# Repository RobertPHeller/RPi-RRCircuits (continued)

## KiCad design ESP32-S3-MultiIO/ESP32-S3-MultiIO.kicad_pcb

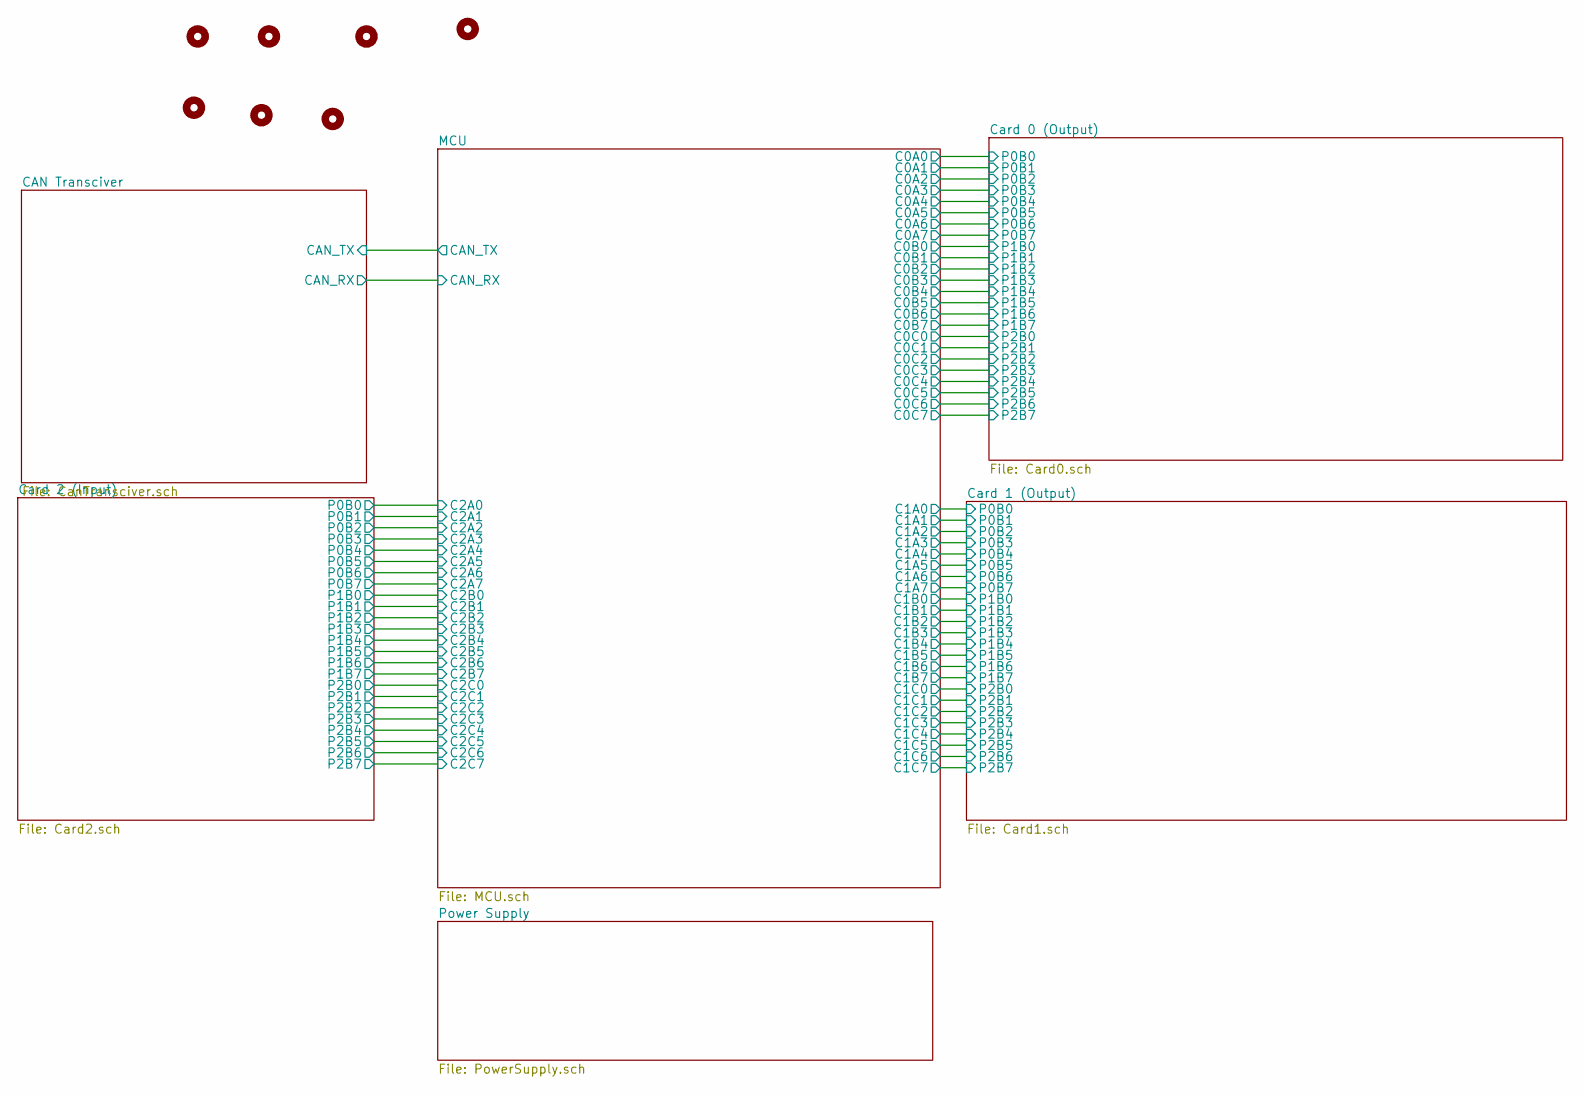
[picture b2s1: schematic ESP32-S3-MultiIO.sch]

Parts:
FD101, FD102, FD103: Fid Mark; Fiducial_Modern_SilkscreenTop
MK101, MK102, MK103, MK104: Mounting_Hole; MountingHole_3.5mm

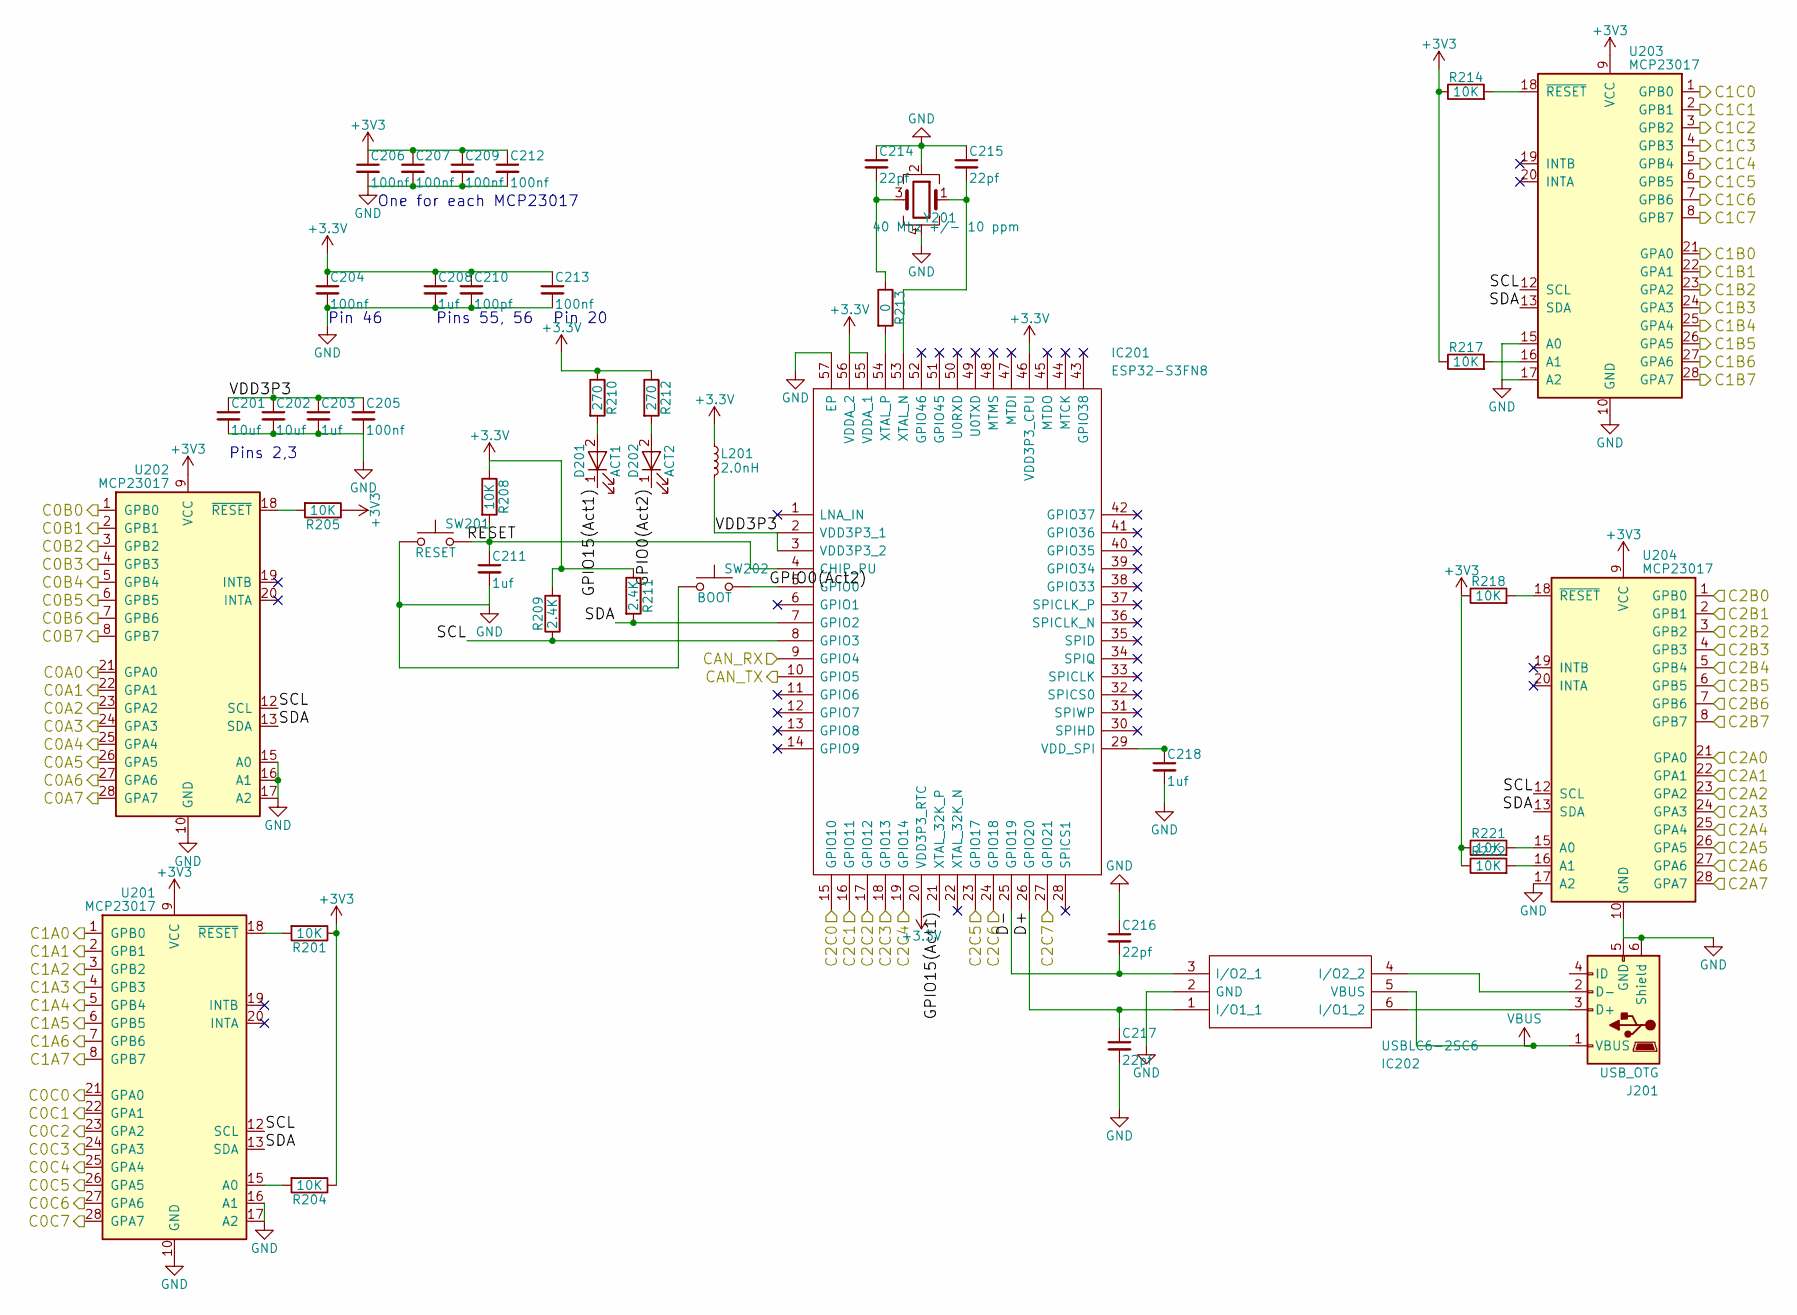
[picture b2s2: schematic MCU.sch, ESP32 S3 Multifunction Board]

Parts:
C201, C202: 10uf; C_0805; Mouser Part Number 187-CL21A106MQFNNNE
C203, C208, C211, C218: 1uf; C_0402; Mouser Part Number 80-C0402C101K8RAUTO
C204, C205, C206, C207, C209, C212, C213: 100nf; C_0402; Mouser Part Number 710-885012105001
C210: 100pf; C_0402; Mouser Part Number 80-C0402C101K3RAUTO
C214, C215, C216, C217: 22pf; C_0402; Mouser Part Number 187-CL05C220JB5NNND
D201: ACT1; LED_0402; Mouser Part Number 710-150040GS73220
D202: ACT2; LED_0402; Mouser Part Number 710-150040SS73220
IC201: ESP32-S3FN8; QFN-56-1EP_7x7mm_Pitch0.4mm; Manufacturer_Part_Number ESP32-S3FN8; Mouser Part Number 356-ESP32-S3FN8
IC202: USBLC6-2SC6; SOT-23-6; Mouser Part Number 511-USBLC6-2SC6
J201: USB_OTG; USB_Micro-B_Molex_47346-0001; Mouser Part Number 538-47346-0001
L201: 2.0nH; L_0402; Mouser Part Number 810-MLG1005S2N0ST000
R201, R204, R205, R208, R214, R217, R218, R221, R222: 10K; R_0402; Mouser Part Number 603-RC0402JR-1310KL
R209, R211: 2.4K; R_0402; Mouser Part Number 71-CRCW06032K40JNEAC
R210, R212: 270; R_0402; Mouser Part Number 754-RR0510P-271D
R213: 0; R_0402; Mouser Part Number 71-CRCW04020000Z0EDC
SW201: RESET; PTS647SM38SMTR2LFS; Mouser Part Number 611-PTS647SN70SMTR2L
SW202: BOOT; PTS647SM38SMTR2LFS; Mouser Part Number 611-PTS647SN70SMTR2L
U201, U202, U203, U204: MCP23017; SOIC-28W_7.5x17.9mm_Pitch1.27mm
Y201: 40 Mhz +/- 10 ppm; FA20_H; Mouser Part Number 732-FA-20H40MF10Z-W3

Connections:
/CAN Transciver/CAN_RX: IC201.9 (GPIO4); also elsewhere on the board
/CAN Transciver/CAN_TX: IC201.10 (GPIO5); also elsewhere on the board
/MCU/C0A0: U202.21 (GPA0); also elsewhere on the board
/MCU/C0A1: U202.22 (GPA1); also elsewhere on the board
/MCU/C0A2: U202.23 (GPA2); also elsewhere on the board
/MCU/C0A3: U202.24 (GPA3); also elsewhere on the board
/MCU/C0A4: U202.25 (GPA4); also elsewhere on the board
/MCU/C0A5: U202.26 (GPA5); also elsewhere on the board
/MCU/C0A6: U202.27 (GPA6); also elsewhere on the board
/MCU/C0A7: U202.28 (GPA7); also elsewhere on the board
/MCU/C0B0: U202.1 (GPB0); also elsewhere on the board
/MCU/C0B1: U202.2 (GPB1); also elsewhere on the board
/MCU/C0B2: U202.3 (GPB2); also elsewhere on the board
/MCU/C0B3: U202.4 (GPB3); also elsewhere on the board
/MCU/C0B4: U202.5 (GPB4); also elsewhere on the board
/MCU/C0B5: U202.6 (GPB5); also elsewhere on the board
/MCU/C0B6: U202.7 (GPB6); also elsewhere on the board
/MCU/C0B7: U202.8 (GPB7); also elsewhere on the board
/MCU/C0C0: U201.21 (GPA0); also elsewhere on the board
/MCU/C0C1: U201.22 (GPA1); also elsewhere on the board
/MCU/C0C2: U201.23 (GPA2); also elsewhere on the board
/MCU/C0C3: U201.24 (GPA3); also elsewhere on the board
/MCU/C0C4: U201.25 (GPA4); also elsewhere on the board
/MCU/C0C5: U201.26 (GPA5); also elsewhere on the board
/MCU/C0C6: U201.27 (GPA6); also elsewhere on the board
/MCU/C0C7: U201.28 (GPA7); also elsewhere on the board
/MCU/C1A0: U201.1 (GPB0); also elsewhere on the board
/MCU/C1A1: U201.2 (GPB1); also elsewhere on the board
/MCU/C1A2: U201.3 (GPB2); also elsewhere on the board
/MCU/C1A3: U201.4 (GPB3); also elsewhere on the board
/MCU/C1A4: U201.5 (GPB4); also elsewhere on the board
/MCU/C1A5: U201.6 (GPB5); also elsewhere on the board
/MCU/C1A6: U201.7 (GPB6); also elsewhere on the board
/MCU/C1A7: U201.8 (GPB7); also elsewhere on the board
/MCU/C1B0: U203.21 (GPA0); also elsewhere on the board
/MCU/C1B1: U203.22 (GPA1); also elsewhere on the board
/MCU/C1B2: U203.23 (GPA2); also elsewhere on the board
/MCU/C1B3: U203.24 (GPA3); also elsewhere on the board
/MCU/C1B4: U203.25 (GPA4); also elsewhere on the board
/MCU/C1B5: U203.26 (GPA5); also elsewhere on the board
/MCU/C1B6: U203.27 (GPA6); also elsewhere on the board
/MCU/C1B7: U203.28 (GPA7); also elsewhere on the board
/MCU/C1C0: U203.1 (GPB0); also elsewhere on the board
/MCU/C1C1: U203.2 (GPB1); also elsewhere on the board
/MCU/C1C2: U203.3 (GPB2); also elsewhere on the board
/MCU/C1C3: U203.4 (GPB3); also elsewhere on the board
/MCU/C1C4: U203.5 (GPB4); also elsewhere on the board
/MCU/C1C5: U203.6 (GPB5); also elsewhere on the board
/MCU/C1C6: U203.7 (GPB6); also elsewhere on the board
/MCU/C1C7: U203.8 (GPB7); also elsewhere on the board
/MCU/C2A0: U204.21 (GPA0); also elsewhere on the board
/MCU/C2A1: U204.22 (GPA1); also elsewhere on the board
/MCU/C2A2: U204.23 (GPA2); also elsewhere on the board
/MCU/C2A3: U204.24 (GPA3); also elsewhere on the board
/MCU/C2A4: U204.25 (GPA4); also elsewhere on the board
/MCU/C2A5: U204.26 (GPA5); also elsewhere on the board
/MCU/C2A6: U204.27 (GPA6); also elsewhere on the board
/MCU/C2A7: U204.28 (GPA7); also elsewhere on the board
/MCU/C2B0: U204.1 (GPB0); also elsewhere on the board
/MCU/C2B1: U204.2 (GPB1); also elsewhere on the board
/MCU/C2B2: U204.3 (GPB2); also elsewhere on the board
/MCU/C2B3: U204.4 (GPB3); also elsewhere on the board
/MCU/C2B4: U204.5 (GPB4); also elsewhere on the board
/MCU/C2B5: U204.6 (GPB5); also elsewhere on the board
/MCU/C2B6: U204.7 (GPB6); also elsewhere on the board
/MCU/C2B7: U204.8 (GPB7); also elsewhere on the board
/MCU/C2C0: IC201.15 (GPIO10); also elsewhere on the board
/MCU/C2C1: IC201.16 (GPIO11); also elsewhere on the board
/MCU/C2C2: IC201.17 (GPIO12); also elsewhere on the board
/MCU/C2C3: IC201.18 (GPIO13); also elsewhere on the board
/MCU/C2C4: IC201.19 (GPIO14); also elsewhere on the board
/MCU/C2C5: IC201.23 (GPIO17); also elsewhere on the board
/MCU/C2C6: IC201.24 (GPIO18); also elsewhere on the board
/MCU/C2C7: IC201.27 (GPIO21); also elsewhere on the board
/MCU/D+: C217.1, IC201.26 (GPIO20), IC202.1 (I/O1_1)
/MCU/D-: C216.2, IC201.25 (GPIO19), IC202.3 (I/O2_1)
/MCU/GPIO0(Act2): D202.1 (K), IC201.5 (GPIO0), SW202.2
/MCU/GPIO15(Act1): D201.1 (K), IC201.21 (XTAL_32K_P)
/MCU/RESET: C211.1, IC201.4 (CHIP_PU), R208.2, SW201.2
/MCU/SCL: IC201.8 (GPIO3), R209.1, U201.12 (SCL), U202.12 (SCL), U203.12 (SCL), U204.12 (SCL)
/MCU/SDA: IC201.7 (GPIO2), R211.2, U201.13 (SDA), U202.13 (SDA), U203.13 (SDA), U204.13 (SDA)
/MCU/VDD3P3: C201.1, C202.1, C203.1, C205.1, IC201.2 (VDD3P3_1), IC201.3 (VDD3P3_2), L201.2
GND: C201.2, C202.2, C203.2, C204.2, C205.2, C206.2, C207.2, C208.2, C209.2, C210.2, C211.2, C212.2, C213.2, C214.1, C215.1, C216.1, C217.2, C218.2, IC201.57 (EP), IC202.2 (GND), J201.5 (GND), J201.6 (Shield), SW201.1, SW202.1, U201.10 (GND), U201.16 (A1), U201.17 (A2), U202.10 (GND), U202.15 (A0), U202.16 (A1), U202.17 (A2), U203.10 (GND), U203.15 (A0), U203.17 (A2), U204.10 (GND), U204.17 (A2), Y201.2, Y201.4; also elsewhere on the board
unnamed: C214.2, R213.1, Y201.3
unnamed: C215.2, IC201.53 (XTAL_N), Y201.1
unnamed: C218.1, IC201.29 (VDD_SPI)
unnamed: D201.2 (A), R210.2
unnamed: D202.2 (A), R212.2
unnamed: IC201.54 (XTAL_P), R213.2
unnamed: IC202.4 (I/O2_2), J201.2 (D-)
unnamed: IC202.6 (I/O1_2), J201.3 (D+)
unnamed: R201.2, U201.18 (~RESET)
unnamed: R204.2, U201.15 (A0)
unnamed: R205.2, U202.18 (~RESET)
unnamed: R214.2, U203.18 (~RESET)
unnamed: R217.2, U203.16 (A1)
unnamed: R218.2, U204.18 (~RESET)
unnamed: R221.2, U204.15 (A0)
unnamed: R222.2, U204.16 (A1)
VBUS: IC202.5 (VBUS), J201.1 (VBUS)

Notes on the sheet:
Pins 2,3
Pin 46
Pins 55, 56
Pin 20
One for each MCP23017

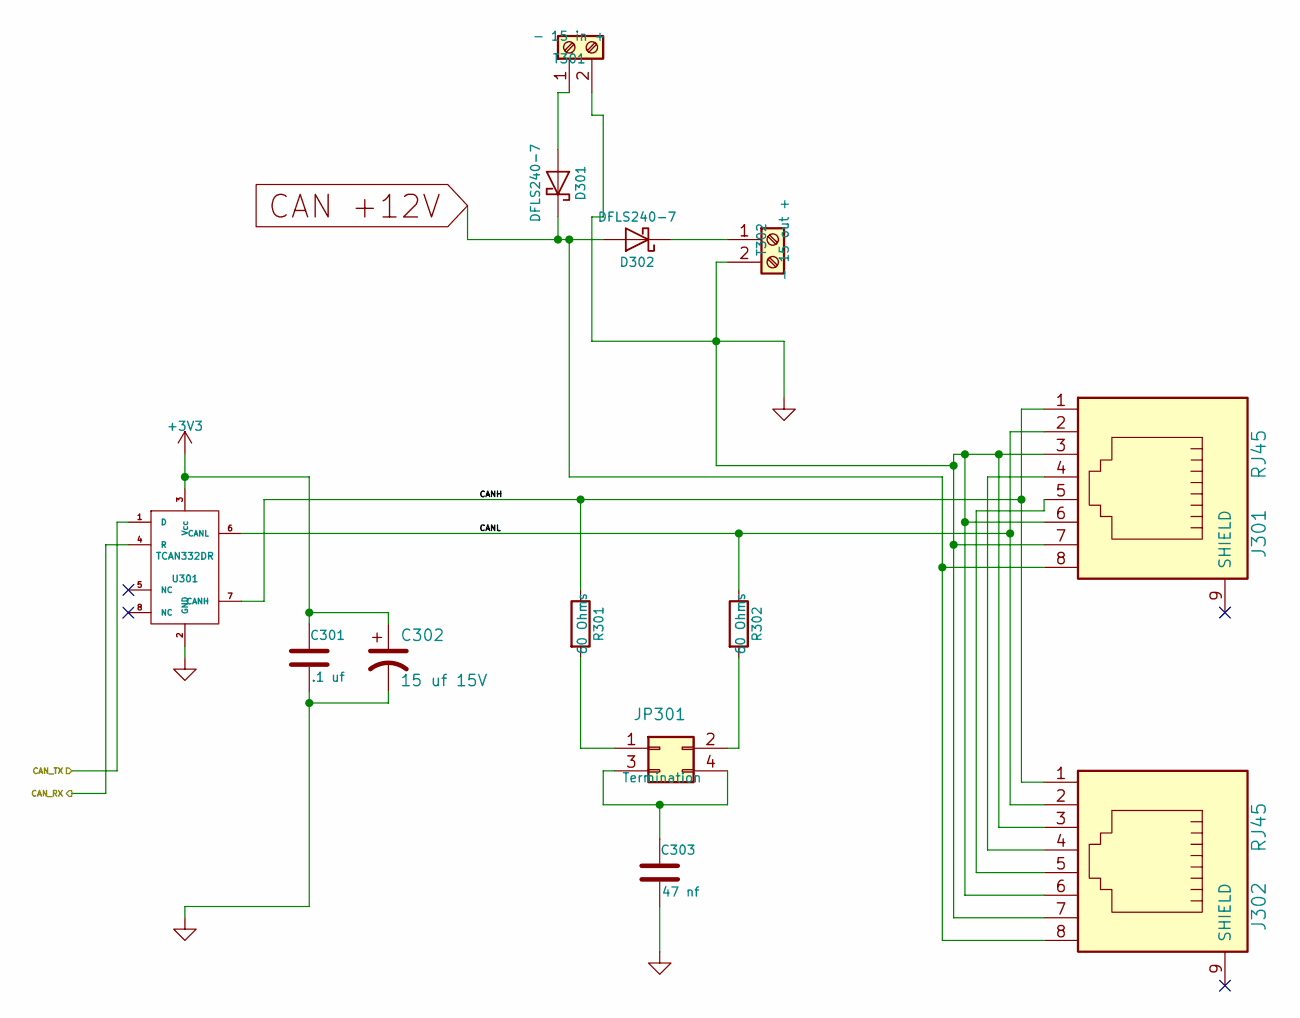
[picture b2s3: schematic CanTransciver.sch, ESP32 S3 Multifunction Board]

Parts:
C301: .1 uf; C_0603; Mouser Part Number 710-885012206095
C302: 15 uf 15V; CP_Elec_4x5.7; Mouser Part Number 647-UUD1C150MCL
C303: 47 nf; C_0603; Mouser Part Number 710-885012206093
D301, D302: DFLS240-7; D_PowerDI-123; Mouser Part Number 621-DFLS240-7
J301, J302: RJ45; RJ45_8N-S; Mouser Part Number 710-615008144221
JP301: Termination; Pin_Header_Straight_2x02_Pitch2.54mm; Mouser Part Number 649-67997-404HLF
R301, R302: 60 Ohms; R_1206; Mouser Part Number 71-CRCW120660R0KNAIF
T301: - 15 in +; TerminalBlock_Pheonix_MPT-2.54mm_2pol; Mouser Part Number 651-1725656
T302: - 15 out +; TerminalBlock_Pheonix_MPT-2.54mm_2pol; Mouser Part Number 651-1725656
U301: TCAN332DR; SOIC-8_3.9x4.9mm_Pitch1.27mm; Mouser Part Number 595-TCAN332DR

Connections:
/CAN Transciver/CANH: J301.1, J302.1, R301.1, U301.7 (CANH)
/CAN Transciver/CANL: J301.2, J302.2, R302.1, U301.6 (CANL)
/CAN Transciver/CAN_RX: U301.4 (R); also elsewhere on the board
/CAN Transciver/CAN_TX: U301.1 (D); also elsewhere on the board
CAN +12V: D301.1 (K), D302.2 (A), J301.8, J302.8; also elsewhere on the board
GND: C301.2, C302.2, C303.2, J301.3, J301.6, J301.7, J302.3, J302.6, J302.7, T301.2, T302.2, U301.2 (GND); also elsewhere on the board
unnamed: C303.1, JP301.3, JP301.4
unnamed: D301.2 (A), T301.1
unnamed: D302.1 (K), T302.1
unnamed: J301.4, J302.4
unnamed: J301.5, J302.5
unnamed: JP301.1, R301.2
unnamed: JP301.2, R302.2

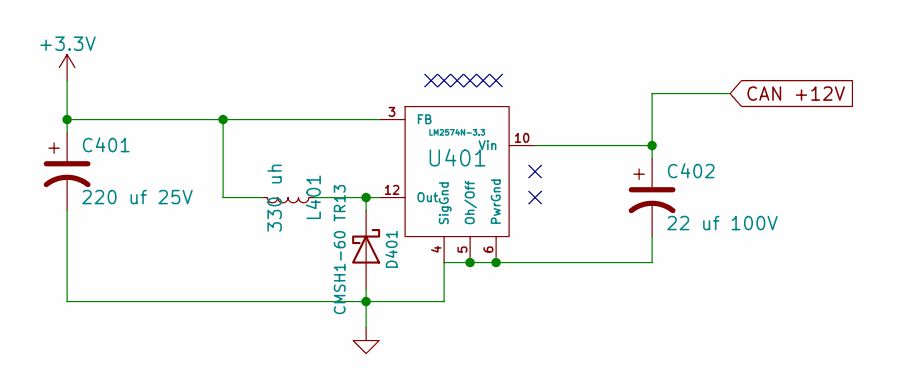
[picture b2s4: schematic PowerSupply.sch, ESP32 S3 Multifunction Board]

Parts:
C401: 220 uf 25V; CP_Elec_8x10; Mouser Part Number 647-UWT1E221MNL1GS
C402: 22 uf 100V; CP_Elec_8x10; Mouser Part Number 647-UUX2A220MNL6GS
D401: CMSH1-60 TR13; D_SMB; Mouser Part Number 610-CMSH1-60TR13
L401: 330 uh; SRN1060; Mouser Part Number 652-SRN1060-331M
U401: LM2574N-3.3; SOIC-14_7.4x8.7mm_Pitch1.27mm; Mouser Part Number 926-LM2574MX33NOPB

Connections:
CAN +12V: C402.1, U401.10 (Vin); also elsewhere on the board
GND: C401.2, C402.2, D401.2 (A), U401.4 (SigGnd), U401.5 (Oh/Off), U401.6 (PwrGnd); also elsewhere on the board
unnamed: D401.1 (K), L401.1, U401.12 (Out)

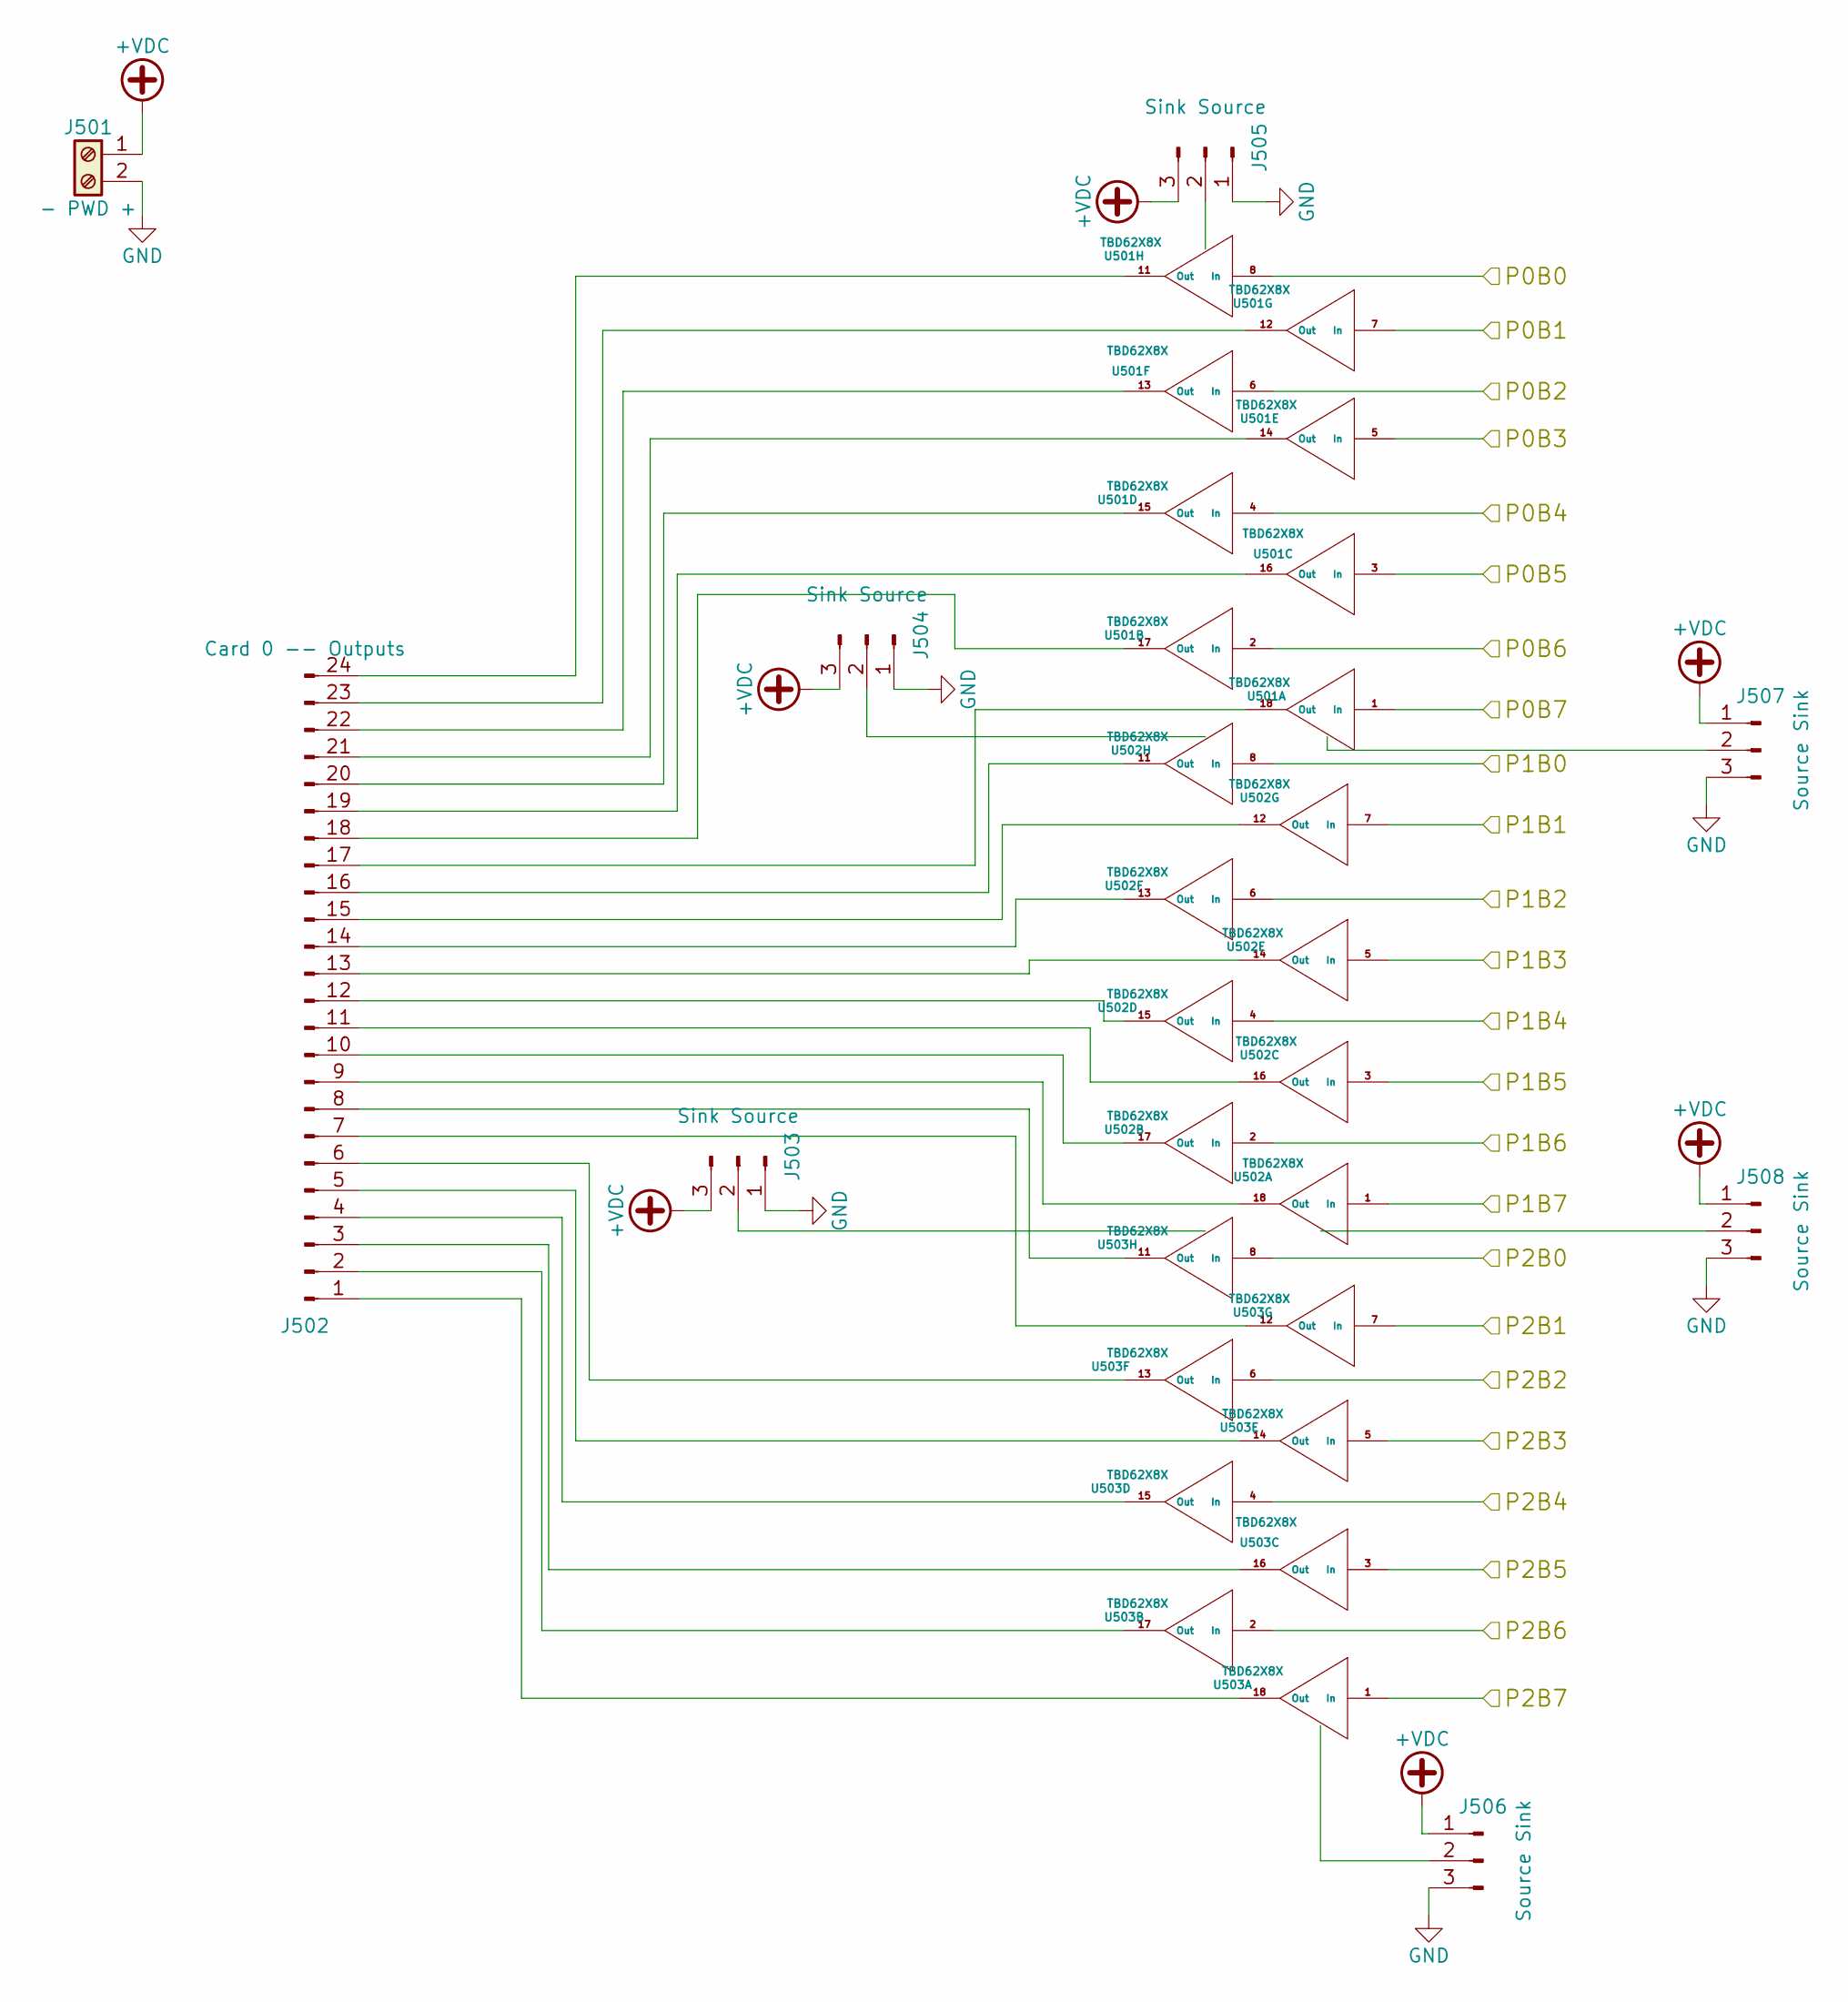
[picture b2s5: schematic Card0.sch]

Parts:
J501: - PWD +; TerminalBlock_Pheonix_MPT-2.54mm_2pol
J502: Card 0 -- Outputs; Molex_KK_396_01x24_3.96mm_RightAngle; Mouser Part Number 538-26-48-1242
J503, J504, J505: Sink Source; Pin_Header_Straight_1x03_Pitch2.54mm
J506, J507, J508: Source Sink; Pin_Header_Straight_1x03_Pitch2.54mm
U501, U502, U503: TBD62X8X; DIP-18_W7.62mm; Mouser Part Number 571-1-2199298-5

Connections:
+VDC: J501.1, J503.3, J504.3, J505.3, J506.1, J507.1, J508.1; also elsewhere on the board
/MCU/C0A0: U501.8 (In); also elsewhere on the board
/MCU/C0A1: U501.7 (In); also elsewhere on the board
/MCU/C0A2: U501.6 (In); also elsewhere on the board
/MCU/C0A3: U501.5 (In); also elsewhere on the board
/MCU/C0A4: U501.4 (In); also elsewhere on the board
/MCU/C0A5: U501.3 (In); also elsewhere on the board
/MCU/C0A6: U501.2 (In); also elsewhere on the board
/MCU/C0A7: U501.1 (In); also elsewhere on the board
/MCU/C0B0: U502.8 (In); also elsewhere on the board
/MCU/C0B1: U502.7 (In); also elsewhere on the board
/MCU/C0B2: U502.6 (In); also elsewhere on the board
/MCU/C0B3: U502.5 (In); also elsewhere on the board
/MCU/C0B4: U502.4 (In); also elsewhere on the board
/MCU/C0B5: U502.3 (In); also elsewhere on the board
/MCU/C0B6: U502.2 (In); also elsewhere on the board
/MCU/C0B7: U502.1 (In); also elsewhere on the board
/MCU/C0C0: U503.8 (In); also elsewhere on the board
/MCU/C0C1: U503.7 (In); also elsewhere on the board
/MCU/C0C2: U503.6 (In); also elsewhere on the board
/MCU/C0C3: U503.5 (In); also elsewhere on the board
/MCU/C0C4: U503.4 (In); also elsewhere on the board
/MCU/C0C5: U503.3 (In); also elsewhere on the board
/MCU/C0C6: U503.2 (In); also elsewhere on the board
/MCU/C0C7: U503.1 (In); also elsewhere on the board
GND: J501.2, J503.1, J504.1, J505.1, J506.3, J507.3, J508.3; also elsewhere on the board
unnamed: J502.1, U503.18 (Out)
unnamed: J502.2, U503.17 (Out)
unnamed: J502.3, U503.16 (Out)
unnamed: J502.4, U503.15 (Out)
unnamed: J502.5, U503.14 (Out)
unnamed: J502.6, U503.13 (Out)
unnamed: J502.7, U503.12 (Out)
unnamed: J502.8, U503.11 (Out)
unnamed: J502.9, U502.18 (Out)
unnamed: J502.10, U502.17 (Out)
unnamed: J502.11, U502.16 (Out)
unnamed: J502.12, U502.15 (Out)
unnamed: J502.13, U502.14 (Out)
unnamed: J502.14, U502.13 (Out)
unnamed: J502.15, U502.12 (Out)
unnamed: J502.16, U502.11 (Out)
unnamed: J502.17, U501.18 (Out)
unnamed: J502.18, U501.17 (Out)
unnamed: J502.19, U501.16 (Out)
unnamed: J502.20, U501.15 (Out)
unnamed: J502.21, U501.14 (Out)
unnamed: J502.22, U501.13 (Out)
unnamed: J502.23, U501.12 (Out)
unnamed: J502.24, U501.11 (Out)
unnamed: J503.2, U503.10 (OC)
unnamed: J504.2, U502.10 (OC)
unnamed: J505.2, U501.10 (OC)
unnamed: J506.2, U503.9 (IC)
unnamed: J507.2, U501.9 (IC)
unnamed: J508.2, U502.9 (IC)
